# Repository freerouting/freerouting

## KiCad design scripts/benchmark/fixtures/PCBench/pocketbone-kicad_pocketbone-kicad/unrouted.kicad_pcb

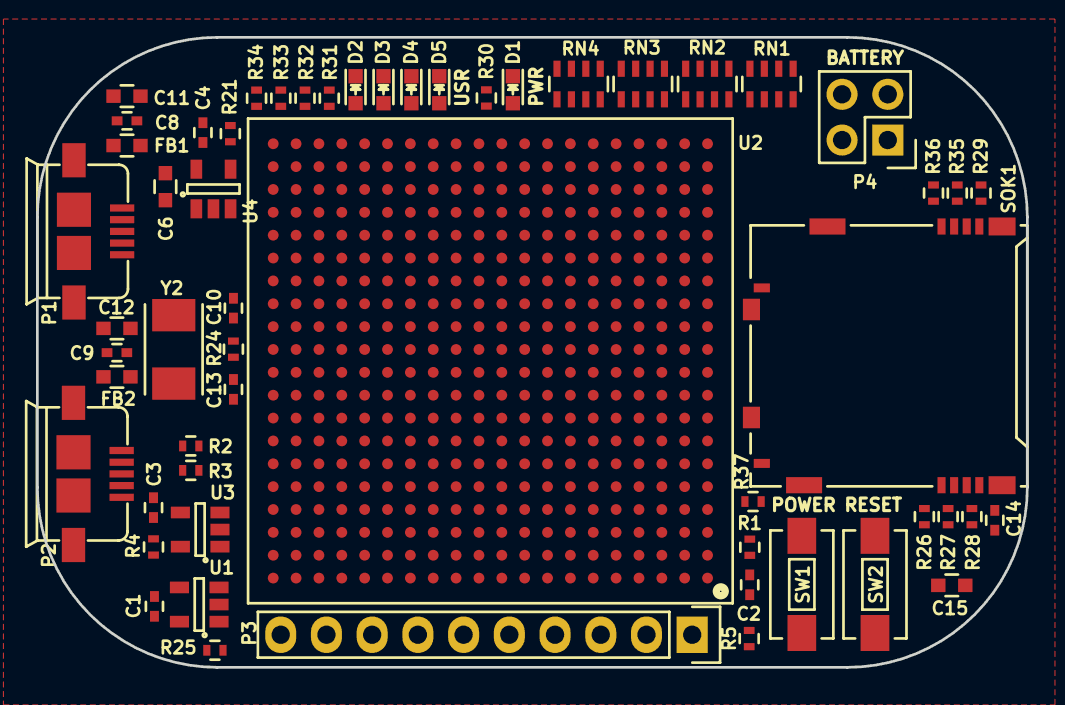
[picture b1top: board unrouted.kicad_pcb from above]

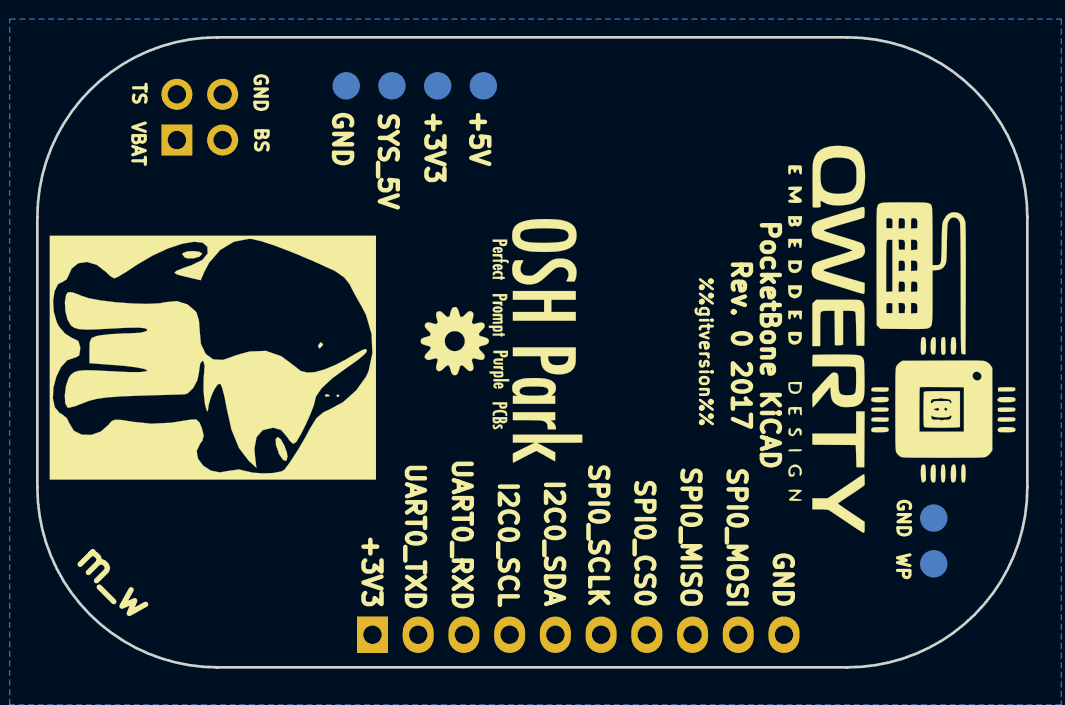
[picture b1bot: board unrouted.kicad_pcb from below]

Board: 4 copper layers, 55.0 x 35.0 mm, 62 parts (6 on the bottom side), 74 nets, no tracks yet.

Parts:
C1, C3, C4, C8, C9, C14: 0.1uF; C_0402
C2: 1uF; C_0402
C6, C11, C12, C15: 10uF; C_0603
C10, C13: 18pF; C_0402
D1, D2, D3, D4, D5: BLUE; LED-0603
FB1, FB2: FILTER; C_0603
P1, P2: USB_OTG; USB_MICRO_B_ST-USB-001E
P3: CONN_01X10; Socket_Strip_Straight_1x10
P4: CONN_02X02; Socket_Strip_Straight_2x02
R1, R5, R26, R27, R28, R29, R35, R36, R37: 10K; R_0402
R2, R3, R4: 1.5K; R_0402
R21: 100K; R_0402
R24: 1M; R_0402
R25: 4.87K; R_0402
R30: 4.7K; R_0402
R31, R32, R33, R34: 240; R_0402
RN1, RN2, RN3, RN4: 100K; R_Array_Concave_4x0603
SOK1: SCHA5B0200
SW1, SW2: SW_PUSH_SMALL_H; SW_SPST_EVQPE1
TP1: 5V; Measurement_Point_Round-SMD-Pad_Small
TP2: WP; Measurement_Point_Round-SMD-Pad_Small
TP3, TP6: GND; Measurement_Point_Round-SMD-Pad_Small
TP4: 3P3; Measurement_Point_Round-SMD-Pad_Small
TP5: SYS_5V; Measurement_Point_Round-SMD-Pad_Small
U1: SN74LVC1G07; SOT-23-5
U2: OSD3358; BGA-400-1-27mm
U3: 24LC32AT-I/OT; SOT-23-5
U4: TPS2051C; SOT-23-5
Y2: 24MHz; 445C33D24M00000

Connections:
3P3AUX: D1.2, U2.Y11
+3V3: C3.1, C14.1, C15.1, P3.1, R1.1, R2.1, R3.1, R4.1, R26.1, R27.1, R28.1, R29.1, R35.1, R36.1, R37.1, RN2.5, RN2.6, RN2.7, RN2.8, SOK1.4, U2.U20, U2.V20, U3.4
+5V: TP1.1, U2.Y5, U2.Y6
BAT_SENSE: P4.3, U2.Y1
GND: C1.2, C2.2, C3.2, C4.2, C6.2, C8.2, C9.2, C11.2, C12.2, C14.2, C15.2, P1.5, P1.6, P2.5, P2.6, P3.10, P4.4, R5.2, R21.2, R25.1, R30.1, R31.1, R32.1, R33.1, R34.1, RN1.1, RN1.2, RN1.3, RN1.4, RN3.1, RN3.2, RN3.3, RN3.4, RN4.1, RN4.2, RN4.3, RN4.4, SOK1.6, SOK1.10, SOK1.11, SW1.1, SW2.1, TP3.1, TP6.1, U1.3, U2.A1, U2.J6, U2.L19, U2.M10, U2.M19, U2.N7, U2.V1, U2.V19, U2.W2, U2.W11, U2.W20, U2.Y18, U3.2, U4.2
I2C0_SCL: P3.4, R2.2, U2.C16, U2.C20, U3.1
I2C0_SDA: P3.5, R3.2, U2.C17, U2.C19, U3.3
MMC0_CD: R37.2, SOK1.9, U2.C15
MMC0_CLK: R29.2, SOK1.5, U2.G17
MMC0_CMD: R28.2, SOK1.3, U2.G18
MMC0_DAT0: R35.2, SOK1.7, U2.G16
MMC0_DAT1: R36.2, SOK1.8, U2.G15
MMC0_DAT2: R26.2, SOK1.1, U2.F18
MMC0_DAT3: R27.2, SOK1.2, U2.F17
unnamed: C2.1, R1.2, SW2.2, U1.4, U2.A10
unnamed: C10.1, R24.2, U2.M20, Y2.1
unnamed: C13.1, R24.1, U2.K20, Y2.2
unnamed: D1.1, R30.2
unnamed: D2.1, R31.2
unnamed: D3.1, R32.2
unnamed: D4.1, R33.2
unnamed: D5.1, R34.2
unnamed: FB1.2, P1.1
unnamed: FB2.2, P2.1
unnamed: R4.2, TP2.1, U3.5
unnamed: R5.1, U2.B4
unnamed: RN1.5, U2.T3
unnamed: RN1.6, U2.R3
unnamed: RN1.7, U2.R2
unnamed: RN1.8, U2.R1
unnamed: RN2.1, U2.R4
unnamed: RN2.2, U2.T1
unnamed: RN2.3, U2.T2
unnamed: RN2.4, U2.V4
unnamed: RN3.5, U2.U3
unnamed: RN3.6, U2.U2
unnamed: RN3.7, U2.U1
unnamed: RN3.8, U2.T4
unnamed: RN4.5, U2.T5
unnamed: RN4.6, U2.V3
unnamed: RN4.7, U2.V2
unnamed: RN4.8, U2.U4
unnamed: SW1.2, U2.D20
unnamed: U2.A19, U2.C5
unnamed: U2.B18, U2.B19
unnamed: U2.B5, U2.B20
unnamed: U2.C6, U2.D19
OSC0_GND: C10.2, C13.2, U2.L20
PMIC_PGOOD: U1.2, U2.A20, U2.B15
SPI_CLK: P3.6, U2.A17
SPI_CS0: P3.7, U2.A16
SPI_MISO: P3.8, U2.B17
SPI_MOSI: P3.9, U2.B16
SYS_5V: C4.1, TP5.1, U2.W4, U2.Y4, U4.5
TRSTN: R25.2, U2.B10
TS: P4.2, U2.W1
UART0_RXD: P3.3, U2.E15
UART0_TXD: P3.2, U2.E16
USB0_D_N: P2.2, U2.N18
USB0_D_P: P2.3, U2.N17
USB0_ID: P2.4, U2.P16
USB0_VBUS: C9.1, C12.1, FB2.1, U2.P15, U2.Y8, U2.Y9
USB1_DRVVBUS: R21.1, U2.F15, U4.4
USB1_D_N: P1.2, U2.R18
USB1_D_P: P1.3, U2.R17
USB1_ID: P1.4, U2.P17
USB1_VBUS: C6.1, C8.1, C11.1, FB1.1, U2.T18, U4.1
USR0_LED: D5.2, U2.V15
USR1_LED: D4.2, U2.U15
USR2_LED: D3.2, U2.T15
USR3_LED: D2.2, U2.V16
VBAT: P4.1, U2.Y2, U2.Y3
VDD_1V8: U2.D10, U2.E9
VDD_RTC: C1.1, U1.5, U2.E14

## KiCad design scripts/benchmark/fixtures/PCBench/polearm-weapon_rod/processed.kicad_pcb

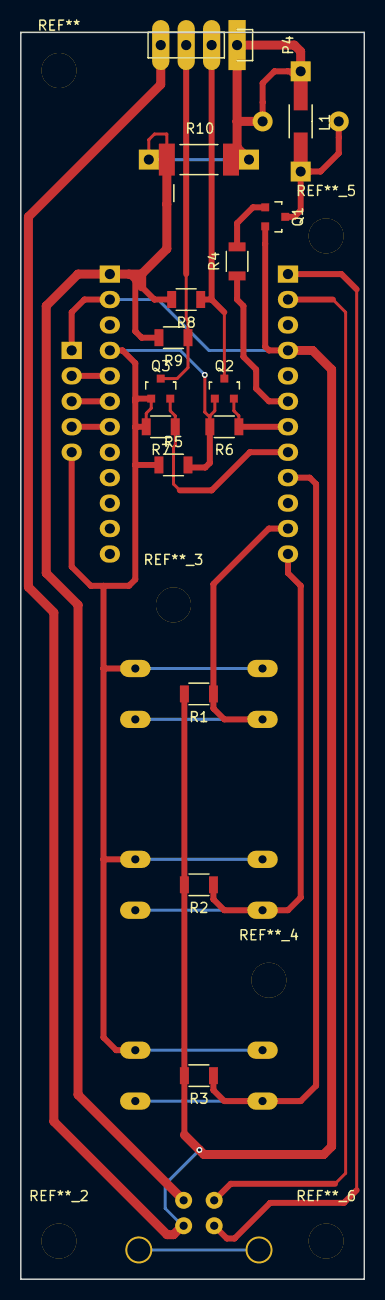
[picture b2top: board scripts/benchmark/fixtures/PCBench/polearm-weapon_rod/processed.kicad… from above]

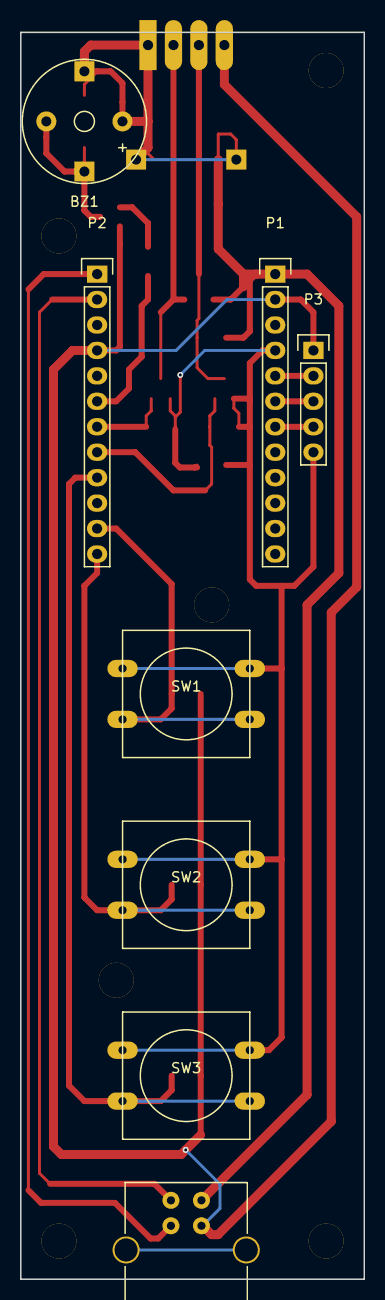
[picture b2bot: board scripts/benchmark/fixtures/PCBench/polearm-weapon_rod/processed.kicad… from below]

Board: 2 copper layers, 34.3 x 124.5 mm, 23 parts (8 on the bottom side), 18 nets.

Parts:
BZ1: buzzer; Buzzer_12x9.5RM7.6
L1: INDUCTOR_SMALL; Resistor_SMD+THTuniversal_1206_RM10_HandSoldering
P1, P2: CONN_01X12; Pin_Header_Straight_1x12
P3: GYRO; Pin_Header_Straight_1x05
P4: DOTSTAR; Pin_Header_Straight_1x04
P5: USB_B
Q1: MMBT3904; SOT-23
Q2, Q3: BSS138; SOT-23
R1, R2, R3, R6, R7: 10K; R_1206
R4, R8, R9: 1K; R_1206
R5: 0; R_1206
R10: 0; Resistor_SMD+THTuniversal_2512_RM10_HandSoldering
SW1: SW_PUSH_R; SW_PUSH-12mm
SW2: SW_PUSH_G; SW_PUSH-12mm
SW3: SW_PUSH_B; SW_PUSH-12mm

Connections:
A1: P1.7, P3.4
A2: P1.6, P3.3
A3: P1.5, P3.2
CLOCK_IN: P4.2, Q2.3, R8.1
D3: P2.6, R4.1
D4: P2.7, Q2.2, R6.1
D5: P2.8, Q3.2, R7.1
D6: P2.9, R3.1, SW3.2
D8: P2.11, R1.1, SW1.2
D9: P2.12, R2.1, SW2.2
DATA_IN: P4.3, Q3.3, R9.1
GND: P1.2, P2.4, P3.1, P4.4, P5.4, Q1.2, R1.2, R2.2, R3.2
unnamed: BZ1.2, L1.2, Q1.3
unnamed: Q1.1, R4.2
RX(Weapon): P2.2, P5.2
TX(Weapon): P2.1, P5.3
V33: P1.4, P3.5, Q2.1, Q3.1, R5.1, R5.2, R6.2, R7.2, SW1.1, SW2.1, SW3.1
V50: BZ1.1, L1.1, P1.1, P4.1, P5.1, R8.2, R9.2, R10.1, R10.2

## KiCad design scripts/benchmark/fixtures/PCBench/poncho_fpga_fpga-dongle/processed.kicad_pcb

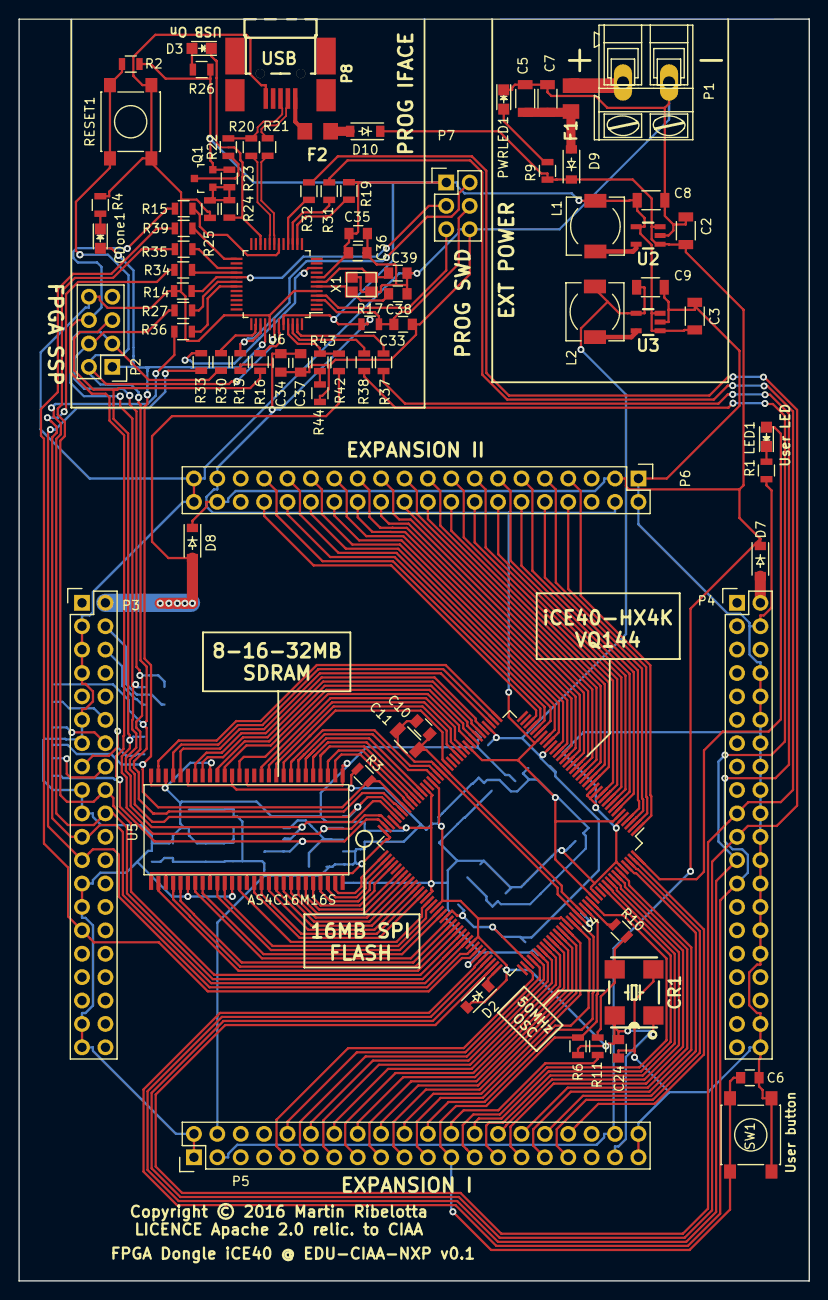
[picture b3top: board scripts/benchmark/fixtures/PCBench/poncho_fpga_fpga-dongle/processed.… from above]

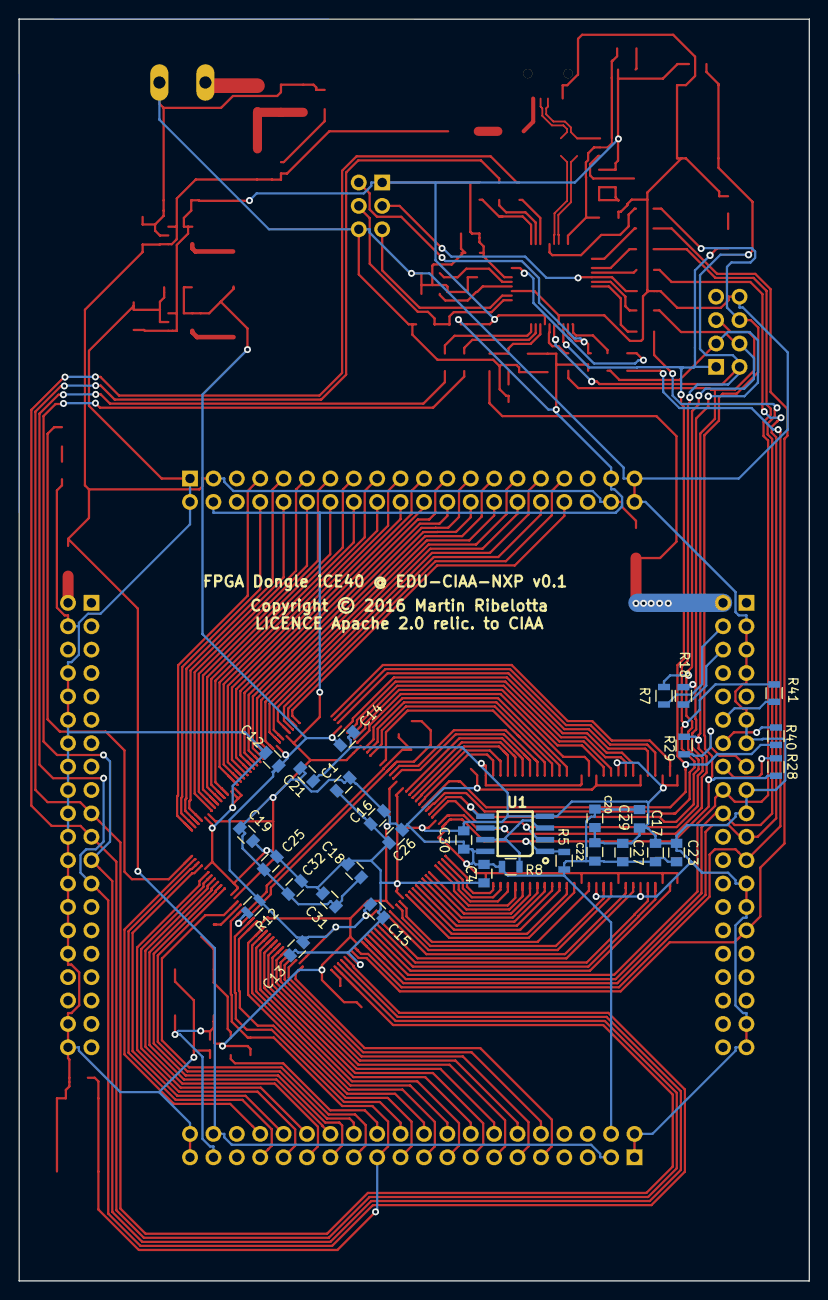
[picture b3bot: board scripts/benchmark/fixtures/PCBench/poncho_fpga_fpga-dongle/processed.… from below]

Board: 2 copper layers, 85.8 x 137.0 mm, 114 parts (31 on the bottom side), 166 nets.

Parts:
C1, C4, C6, C10, C12, C13, C14, C15, C16, C17, C18, C19, C20, C21, C22, C23, C24, C25, C26, C27, C29, C30, C31, C32, C33, C34, C36: 100nF; C_0805
C2, C3: 22uF; C_1206
C5, C7: 47uF; C_1206
C8, C9, C11: 10uF; C_1206
C35, C37: 10nF; C_0805
C38, C39: 18pF; C_0805
CDone1: LED/Green/0805; LED-0805
CR1: Oscillator-50MHZ_TXC-7W; Oscillator_7.0x5.0mm
D2, D7, D8, D9, D10: 1N5819(S4SOD-123); SOD-123
D3: LED/Red/0805; LED-0805
F1, F2: 1A; FUSE-1206
L1, L2: 2.2uH; Choke_SMD_6.3x6.3_H3
LED1: LED/Red/0805; LED-0805
P1: CONN_01X02; AK300-2
P2: PGM; Pin_Header_Straight_2x04
P3: right; Pin_Header_Straight_2x20
P4: left; Pin_Header_Straight_2x20
P5, P6: CONN_01X40; Pin_Header_Straight_2x20
P7: DBG_SWD; Pin_Header_Straight_2x03
P8: USB_PWR; USB_Mini-B-NOSILK
PWRLED1: LED/Red/0805; LED-0805
Q1: BC857; SOT-23
R1, R3, R9, R19, R24, R26: 2.2k; R_0805
R2, R5, R6, R8, R13, R14, R17, R23, R42, R43, R44: 10k; R_0805
R4, R10, R11, R15, R16, R27, R30: 22R; R_0805
R7, R12, R18, R28, R29, R31, R32, R33, R34, R35, R36, R37, R38, R39, R40, R41: 100R; R_0805
R20, R21: 33R; R_0805
R22: 1.5k; R_0805
R25: UL; R_0805
RESET1: T1107A(6x3,8x2,5MM); SW_SPST_PTS645
SW1: T1107A(6x3,8x2,5MM); SW_SPST_PTS645
U1: W25Q128FVSIG(SOIC-8_208mil); SOIC-8_208mil
U2: sc189(Z) 3.3v; SOT-23-5
U3: sc189(C) 1.2v; SOT-23-5
U4: iCE40-HX4K-TQ144; LQFP-144_20x20mm_Pitch0.5mm
U5: AS4C16M16S; TSOP_II_54
U6: LPC11U35FBD48; LQFP-48_7x7mm_Pitch0.5mm
X1: 12MHz; crystal_FA238-TSX3225

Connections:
+1V2: C9.2, C12.1, C13.1, C14.1, C15.1, L2.2, R12.1, U3.4, U4.27, U4.40, U4.92, U4.111
+3V3: C1.2, C3.2, C4.2, C8.2, C16.1, C17.1, C18.1, C19.1, C20.1, C21.1, C22.1, C23.1, C24.1, C25.1, C26.1, C27.1, C29.1, C30.1, C31.1, C32.1, C34.1, C35.1, C36.1, C37.1, CR1.1, CR1.4, D2.2, L1.2, P5.4, P5.37, P6.4, P6.37, P7.1, Q1.2, R2.2, R3.2, R5.2, R6.2, R8.1, R13.1, R17.1, R19.2, R23.1, R26.1, U1.8, U2.4, U3.1, U3.3, U4.6, U4.30, U4.46, U4.57, U4.72, U4.89, U4.100, U4.123, U4.131, U5.1, U5.3, U5.9, U5.14, U5.27, U5.43, U5.49, U6.8, U6.44
+5V: C2.2, D7.1, D8.1, D9.1, D10.1, P5.3, P5.38, P6.3, P6.38, R9.1, U2.1, U2.3
/AUX_CDONE: P3.14, R40.1
/AUX_CRESET: P3.12, R41.1
/AUX_SPI_MISO: P3.4, R7.1
/AUX_SPI_MOSI: P3.6, R18.1
/AUX_SPI_SCK: P3.15, R29.1
/AUX_SPI_SSEL: P3.16, R28.1
/BUT1: C6.2, P5.23, R6.1, SW1.2, U4.128
/CIAA_5V1: D7.2, P4.2
/CIAA_5V2: D8.2, P3.2, R42.2
/DBG_SWCLK: P7.3, R14.1, U6.29
/DBG_SWDIO: P7.2, R13.2, U6.39
/DBG_~ISP~: P7.5, U6.4
/DBG_~RST~: C33.1, P7.4, R17.2, U6.3
/D_USB_N: R21.2, U6.19
/D_USB_P: R20.2, U6.20
/EXTCLK: P5.24, R11.1
/FPGA_IO_BANK1_0: P5.9, U4.110
/FPGA_IO_BANK1_1: P5.10, U4.112
/FPGA_IO_BANK1_2: P5.11, U4.113
/FPGA_IO_BANK1_3: P5.12, U4.114
/FPGA_IO_BANK1_4: P5.13, U4.115
/FPGA_IO_BANK1_5: P5.14, U4.116
/FPGA_IO_BANK1_6: P5.15, U4.117
/FPGA_IO_BANK1_7: P5.16, U4.118
/FPGA_IO_BANK1_8: P5.17, U4.119
/FPGA_IO_BANK1_9: P5.18, U4.120
/FPGA_IO_BANK1_10: P5.19, U4.121
/FPGA_IO_BANK1_11: P5.20, U4.122
/FPGA_IO_BANK1_12: P5.21, U4.124
/FPGA_IO_BANK1_13: P5.22, U4.125
/FPGA_IO_BANK1_14: P5.25, U4.130
/FPGA_IO_BANK1_15: P5.26, U4.134
/FPGA_IO_BANK1_16: P5.27, U4.135
/FPGA_IO_BANK1_17: P5.28, U4.136
/FPGA_IO_BANK1_18: P5.29, U4.137
/FPGA_IO_BANK1_19: P5.30, U4.138
/FPGA_IO_BANK1_20: P5.31, U4.139
/FPGA_IO_BANK1_21: P5.32, U4.141
/FPGA_IO_BANK1_22: P5.33, U4.142
/FPGA_IO_BANK1_23: P5.34, U4.143
/FPGA_IO_BANK2_0: P6.7, U4.1
/FPGA_IO_BANK2_1: P6.8, U4.2
/FPGA_IO_BANK2_2: P6.9, U4.3
/FPGA_IO_BANK2_3: P6.10, U4.4
/FPGA_IO_BANK2_4: P6.11, U4.7
/FPGA_IO_BANK2_5: P6.12, U4.8
/FPGA_IO_BANK2_6: P6.13, U4.9
/FPGA_IO_BANK2_7: P6.14, U4.10
/FPGA_IO_BANK2_8: P6.15, U4.11
/FPGA_IO_BANK2_9: P6.16, U4.12
/FPGA_IO_BANK2_10: P6.17, U4.15
/FPGA_IO_BANK2_11: P6.18, U4.16
/FPGA_IO_BANK2_12: P6.19, U4.17
/FPGA_IO_BANK2_13: P6.20, U4.18
/FPGA_IO_BANK2_14: P6.21, U4.19
/FPGA_IO_BANK2_15: P6.22, U4.20
/FPGA_IO_BANK2_16: P6.23, U4.21
/FPGA_IO_BANK2_17: P6.24, U4.22
/FPGA_IO_BANK2_18: P6.25, U4.23
/FPGA_IO_BANK2_19: P6.26, U4.24
/FPGA_IO_BANK2_20: P6.27, U4.25
/FPGA_IO_BANK2_21: P6.28, U4.26
/FPGA_IO_BANK2_22: P6.29, U4.28
/FPGA_IO_BANK2_23: P6.30, U4.29
/FPGA_IO_BANK2_24: P6.31, U4.31
/FPGA_IO_BANK2_25: P6.32, U4.32
/FPGA_IO_BANK2_26: P6.33, U4.33
/FPGA_IO_BANK2_27: P6.34, U4.34
/FPGM_MISO: R27.1, U6.30
/FPGM_MOSI: R30.1, U6.38
/FPGM_SCK: R16.1, U6.43
/FPGM_SS: R15.1, U6.18
/GNDPLL: C10.1, C11.1, U4.53, U4.127
/GPIO0: P3.29, R39.2, U4.102
/I2C_SCL: P4.21, R32.2, U4.106
/I2C_SDA: P4.19, R31.2, U4.107
/LED1: LED1.2, U4.144
/P_GPIO: R39.1, U6.25
/P_RxD: R38.1, U6.46
/P_SCL: R32.1, U6.16
/P_SDA: R31.1, U6.15
/P_SPI_CLK: R36.1, U6.31
/P_SPI_MISO: R35.1, U6.27
/P_SPI_MOSI: R34.1, U6.28
/P_SPI_SS: R33.1, U6.10
/P_TxD: R37.1, U6.47
/RAM_A1: U4.76, U5.23
/RAM_A2: U4.75, U5.24
/RAM_A3: U4.74, U5.25
/RAM_A4: U4.73, U5.26
/RAM_A5: U4.64, U5.29
/RAM_A6: U4.63, U5.30
/RAM_A7: U4.62, U5.31
/RAM_A8: U4.61, U5.32
/RAM_A9: U4.60, U5.33
/RAM_A10: U4.56, U5.34
/RAM_A11: U4.78, U5.22
/RAM_A12: U4.55, U5.35
/RAM_A13: U4.52, U5.36
/RAM_A14: U4.80, U5.20
/RAM_A15: U4.79, U5.21
/RAM_CAS: U4.83, U5.17
/RAM_CKE: U4.49, U5.37
/RAM_CLK: U4.48, U5.38
/RAM_CS: U4.81, U5.19
/RAM_D0: U4.96, U5.2
/RAM_D1: U4.95, U5.4
/RAM_D2: U4.94, U5.5
/RAM_D3: U4.93, U5.7
/RAM_D4: U4.91, U5.8
/RAM_D5: U4.90, U5.10
/RAM_D6: U4.88, U5.11
/RAM_D7: U4.87, U5.13
/RAM_D8: U4.45, U5.42
/RAM_D9: U4.44, U5.44
/RAM_D10: U4.43, U5.45
/RAM_D11: U4.42, U5.47
/RAM_D12: U4.41, U5.48
/RAM_D13: U4.39, U5.50
/RAM_D14: U4.38, U5.51
/RAM_D15: U4.37, U5.53
/RAM_DQMH: U4.47, U5.39
/RAM_DQML: U4.85, U5.15
/RAM_RAS: U4.82, U5.18
/RAM_RDnWR: U4.84, U5.16
/RxD: P4.23, R38.2, U4.105
/SPI_CLK: P3.20, R36.2, U4.98
/SPI_CS: P3.23, R33.2, U4.101
/SPI_MISO: P3.18, R35.2, U4.97
/SPI_MOSI: P3.21, R34.2, U4.99
/SYSCLK: R10.1, U4.129
/TxD: P4.25, R37.2, U4.104
/USB_N: P8.2, R21.1
/USB_P: P8.3, R20.1, R22.1
/VCCPLL: C10.2, C11.2, R12.2, U4.54, U4.126
/iCE40-CDONE: CDone1.2, P2.1, R3.1, R40.2, U4.65, U6.40
/iCE40-CRESET: P2.2, R2.1, R41.2, RESET1.2, U4.66, U6.42
/iCE40-SCK: P2.5, R16.2, R29.2, U1.6, U4.70
/iCE40-SDI: P2.3, R18.2, R30.2, U1.2, U4.68
/iCE40-SDO: P2.4, R7.2, R27.2, U1.5, U4.67
/iCE40-SS_B: P2.6, R5.1, R15.2, R28.2, U1.1, U4.71
/~USB_CONNECT~: D3.1, R24.2, U6.22
GND: C1.1, C2.1, C3.1, C4.1, C5.1, C6.1, C7.1, C8.1, C9.1, C12.2, C13.2, C14.2, C15.2, C16.2, C17.2, C18.2, C19.2, C20.2, C21.2, C22.2, C23.2, C24.2, C25.2, C26.2, C27.2, C29.2, C30.2, C31.2, C32.2, C33.2, C34.2, C35.2, C36.2, C37.2, C38.2, C39.2, CR1.2, P1.1, P2.8, P3.3, P3.5, P3.7, P3.11, P3.13, P3.17, P3.19, P3.25, P3.27, P3.37, P3.39, P4.4, P4.8, P4.10, P4.12, P4.14, P4.16, P4.18, P4.20, P4.22, P4.24, P4.26, P4.28, P4.30, P4.32, P4.38, P4.40, P5.1, P5.2, P5.39, P5.40, P6.1, P6.2, P6.39, P6.40, P7.6, P8.5, PWRLED1.1, R1.2, R4.2, R14.2, R25.2, R44.1, RESET1.1, SW1.1, U1.4, U2.2, U3.2, U4.5, U4.13, U4.14, U4.59, U4.69, U4.86, U4.103, U4.132, U4.140, U5.6, U5.12, U5.28, U5.41, U5.46, U5.52, U5.54, U6.5, U6.41, X1.3
unnamed: C5.2, C7.2, D9.2, F1.2
unnamed: C38.1, U6.6, X1.2
unnamed: C39.1, U6.7, X1.1
unnamed: CDone1.1, R4.1
unnamed: CR1.3, R10.2, R11.2
unnamed: D2.1, U4.108
unnamed: D3.2, R26.2
unnamed: D10.2, F2.2
unnamed: F1.1, P1.2
unnamed: F2.1, P8.1
unnamed: L1.1, U2.5
unnamed: L2.1, U3.5
unnamed: LED1.1, R1.1
unnamed: PWRLED1.2, R9.2
unnamed: Q1.1, R23.2, R24.1, R25.1
unnamed: Q1.3, R22.2
unnamed: R8.2, U1.3, U1.7
unnamed: R19.1, U6.14
unnamed: R42.1, R43.1, U6.45
unnamed: R43.2, R44.2

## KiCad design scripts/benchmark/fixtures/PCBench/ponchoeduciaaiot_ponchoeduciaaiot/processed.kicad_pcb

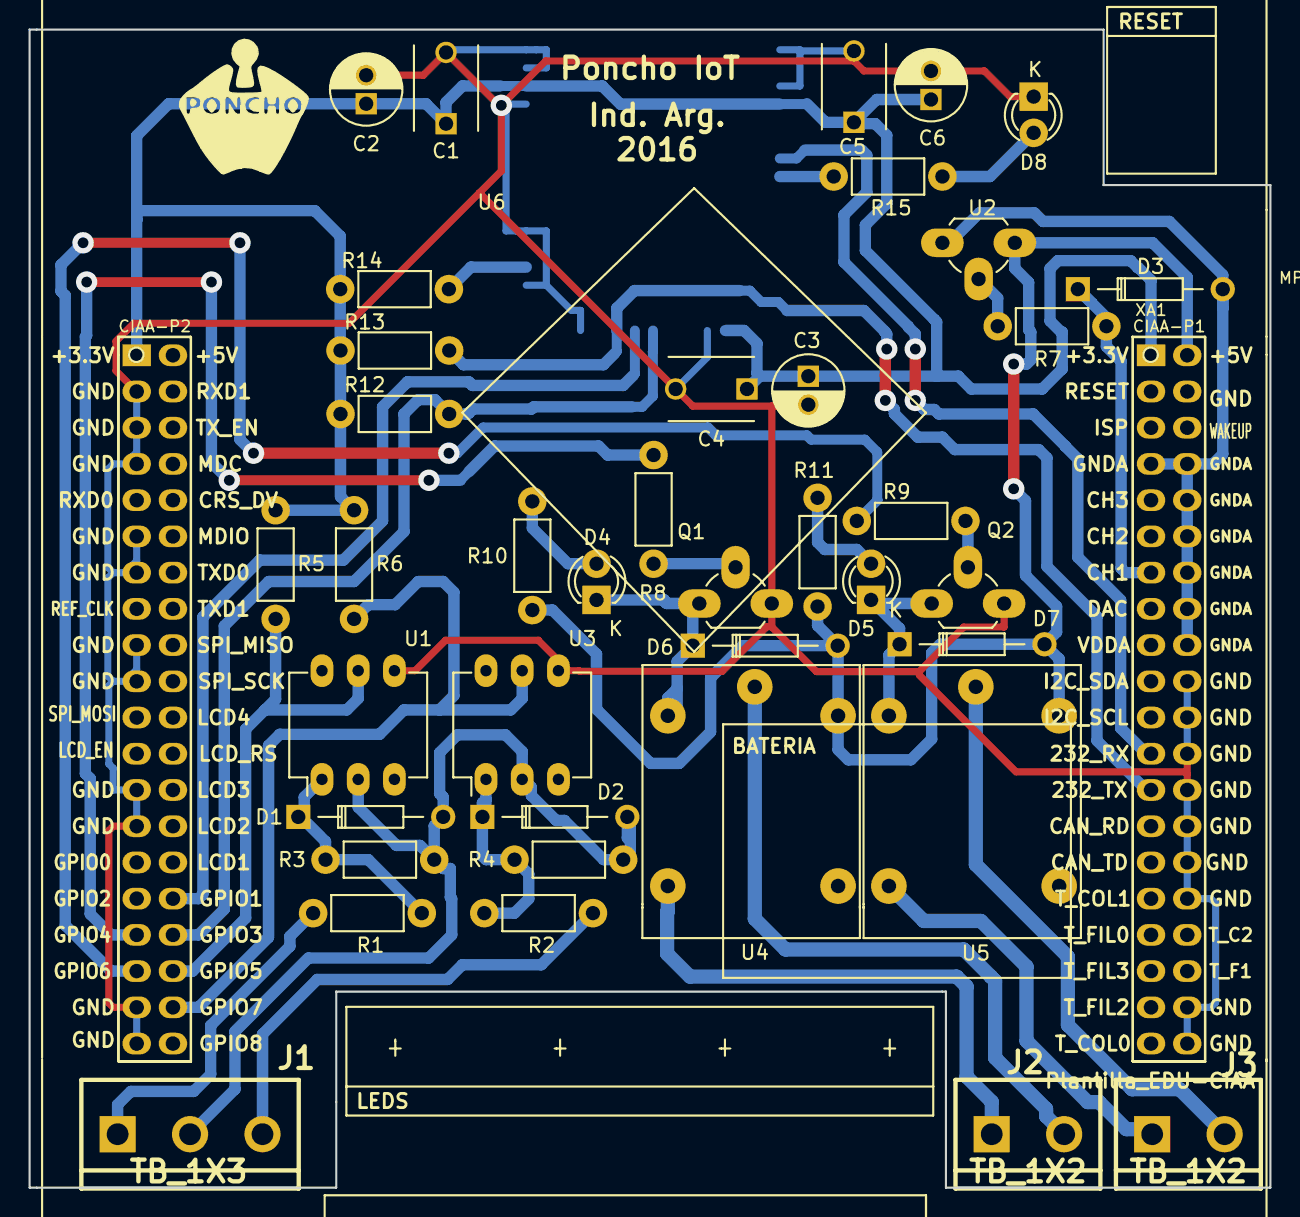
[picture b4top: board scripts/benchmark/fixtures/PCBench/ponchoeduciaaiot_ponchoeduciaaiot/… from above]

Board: 2 copper layers, 87.0 x 81.2 mm, 42 parts (0 on the bottom side), 32 nets.

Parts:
C1, C4, C5: 100nF; C_Disc_D6_P5
C2, C3, C6: 2.2uF; C_Radial_D5_L11_P2
D1, D2, D6, D7: 1N4007; Diode_DO-35_SOD27_Horizontal_RM10
D3: 1N4728A; Diode_DO-35_SOD27_Horizontal_RM10
D4, D5, D8: LED; LED-3MM
J1: TB_1X3; bornier3
J2, J3: TB_1X2; bornier2
MP?: Plantilla_EDU-CIAA
Q1, Q2: BC548; TO-92_Rugged
R1, R2: 3.3k; Resistor_Horizontal_RM7mm
R3, R4: 4.7k; Resistor_Horizontal_RM7mm
R5, R6, R8, R9, R12, R14: 10k; Resistor_Horizontal_RM7mm
R7, R15: 150; Resistor_Horizontal_RM7mm
R10, R11: 330; Resistor_Horizontal_RM7mm
R13: 100k; Resistor_Horizontal_RM7mm
U1, U3: 4N25; DIP-6_W7.62mm_LongPads
U2: LM35; TO-92_Rugged
U4, U5: RELAY; Relay5vSI
U6: RN1810E; RN1810
XA1: Conn_Poncho2P_2x_20x2; Conn_Poncho_Mediano

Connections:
+3V3: C1.1, C2.1, C3.1, C4.1, C5.1, C6.1, R5.1, R6.1, R12.1, R13.1, R14.1, U6.4, U6.15, U6.35, XA1.1, XA1.41
+5V: D6.2, D7.2, R10.1, R11.1, U2.1, U4.2, U5.2, XA1.2
/ConectoresPoncho/ANALOG_IN: D3.1, R7.1, XA1.13
/ConectoresPoncho/MODULE_RESET: R12.2, U6.19, XA1.74
/ConectoresPoncho/RXD_EDUCIAA: U6.7, XA1.23
/ConectoresPoncho/TXD_EDUCIAA: R13.2, U6.21, XA1.25
/comm/CMD_CTRL: U6.20, XA1.72
/gpios/IN0: R5.2, U1.5, XA1.76
/gpios/IN1: R6.2, U3.5, XA1.78
/gpios/OUT0: R8.2, XA1.73
/gpios/OUT1: R9.2, XA1.75
GND: C1.2, C2.2, C3.2, C4.2, C5.2, C6.2, D8.1, Q1.3, Q2.3, U1.4, U3.4, U6.1, U6.3, U6.16, U6.23, U6.24, U6.27, U6.34, U6.36, U6.37, XA1.20, XA1.22, XA1.24, XA1.26, XA1.28, XA1.30, XA1.32, XA1.38, XA1.40, XA1.43, XA1.45, XA1.47, XA1.51, XA1.53, XA1.57, XA1.59, XA1.65, XA1.67, XA1.77, XA1.79
GNDA: D3.2, U2.3, XA1.7, XA1.8, XA1.10, XA1.12, XA1.14, XA1.16, XA1.18
unnamed: D1.1, R1.1, R3.1, U1.1
unnamed: D1.2, D2.2, J1.2, R3.2, R4.2, U1.2, U3.2
unnamed: D2.1, R2.1, R4.1, U3.1
unnamed: D4.1, D6.1, Q1.1, U4.1
unnamed: D4.2, R10.2
unnamed: D5.1, D7.1, Q2.1, U5.1
unnamed: D5.2, R11.2
unnamed: D8.2, R15.1
unnamed: J1.1, R1.2
unnamed: J1.3, R2.2
unnamed: J2.1, U4.4
unnamed: J2.2, U4.3
unnamed: J3.1, U5.4
unnamed: J3.2, U5.3
unnamed: Q1.2, R8.1
unnamed: Q2.2, R9.1
unnamed: R7.2, U2.2
unnamed: R14.2, U6.25
unnamed: R15.2, U6.8

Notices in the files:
scripts/benchmark/fixtures/PCBench/poncho_fpga_fpga-dongle/processed.kicad_pcb:
Copyright © 2016 Martin Ribelotta
scripts/benchmark/fixtures/PCBench/ponchoeduciaaiot_ponchoeduciaaiot/processed.kicad_pcb:
License: GPL3
